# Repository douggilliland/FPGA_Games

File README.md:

# FPGA Games gathered from the Internet

Annotated with the source where I could re-find it again.

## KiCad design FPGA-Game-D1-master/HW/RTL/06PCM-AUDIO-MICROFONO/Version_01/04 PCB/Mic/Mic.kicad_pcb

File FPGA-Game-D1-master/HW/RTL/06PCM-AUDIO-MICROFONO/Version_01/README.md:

# SISTEMA DE AUDIO

## Integrantes del equipo de trabajo:

### 1 Lisseth Tatiana Herrera Rosero ltherreraro@unal.edu.co

### 2 Santiago Esteban Guevara Rozo seguevarar@unal.edu.co

### 3 Michael Fabian Sierra Tarazona mfsierrat@unal.edu.co

## Descripción general del sistema: 

En el módulo de audio se pretende garantizar la grabación de una voz por un lapso aproximado de 2 segundos,  digitalizar, guardar y reproducir esta señal, se utilizaran dos grandes modulos en el cual se tienen microfono y altavoz
En el módulo del micrófono se tendrá una señal análoga con frecuencia de 1 a 5 kHz, la cual entrará a un convertidor A/D, acontinuación se procesará en un filtro pasabajos logrando una salida de 18 bits; Esta entrará a nuestra FPGA nexys4 donde se guardará por módulos en un proceso FIFO sincrónico, el sincronismo de los clocks es necesario para acoplar todas las fases de dicho proceso.
En la segunda etapa (altavoz), entra dicha informacion a un convertidor D/A (PCM) el cual también logra amplificar esta señal para poder ser reproducida.

## Descripción de la caja funcional (Modulo Microfono):
En este módulo depende del modulo divisor de frecuencia. El divisor de frecuencia es necesario para obtener los clocks de sincranización de el módulo de micrófono y de altavoz.

Este modulo tiene entradas: 
* **Data** datos provenientes del micrófono (conformado por 32 bits) de los cuales solo 18 se van a usar para la salida 
* **Enable** para inicializar (conformado por 1 bit)

Este módulo tiene salidas:
* **Clk** El clock que necesita el micrófono para modular la señal y enviarla (conformado por 1 bit)
* **ws** necesario más adelante para seleccionar derecho o izquierdo (conformado por 1 bit)
* **Dataout** datos de salida serializado (conformado por 1 bit)
* **done** para indicar que finalizó la acción (conformado por 1 bit)

Y finalmente tiene un parametro
* **Count** para contar las interacciones 

### Descripción funcional (Módulo Micrófono MEMS):
Para que el modulo de microfono este activo la frecuencia del clk debe estar ser mayor a 1MHz y tener el voltaje VDD activo, pero esto se garantiza en el divisor de frecuencia.

## Descripción de la caja funcional (Modulo Altavoz):
En este módulo tambien depende de el modulo divisor de frecuencia. 

Este modulo tiene entradas: 
* **Data** datos provenientes del micrófono ya serializados (conformado por 1 bit) 
* **Enable** para inicializar (conformado por 1 bit)

Este módulo tiene salidas:
* **Bclk** El clock que necesita el altavoz para recuperar los datos(conformado por 1 bit)
* **LRclk** necesario para seleccionar derecho o izquierdo (conformado por 1 bit)
* **Data_R** datos de salida canal derecho (conformado por 16 bit)
* **Data_L** datos de salida canal izquierdo (conformado por 16 bit)
* **done** para indicar que finalizó la acción (conformado por 1 bit)

Y finalmente tiene un parametro
* **Count** para contar las interacciones 

### Descripción funcional (Módulo Altavoz):
El LRclk tiene un delay de 1 ciclo de Bclk por lo tanto solo soporta frecuencias de 8KHz, 16KHz, 32KHz, 44.1KHz, 48KHz, 88.2KHz y 96KHz, pero esto se garantiza en el divisor de frecuencia.

## Descripción de la caja funcional (Módulo Divisor de frecuencia):
Este modulo tiene entradas: 
* **Clk** El clock que necesita realizar la divison de señal (conformado por 1 bit)
* **Reset** para reiniciar el sistema (conformado por 1 bit)

Este módulo tiene salidas:
* **Clkout** El clock que se deseaba (conformado por 1 bit)
Y finalmente tiene como parametros
* **fi** Frecuencia de entrada
* **fo** Frecuencia de salida (la que se desea obtener)
* **Count** para contar las interacciones 

### Descripción funcional (Divisor de frecuencia):

## Descripción Estructural: 

## Diagrama de Estados:

### Diagrama de estado del MEMS:

### Diagrama de estado del altavoz:

## Arquitectura del periférico:

XXXXXXXXXXXXXXXXXXXXXXXXXXXXXXXXXXXXXXXXXXXXXXXXXX

## Diagrama de bloques del periférico:

XXXXXXXXXXXXXXXXXXXXXXXXXXXXXXXXXXXXXXXXXXXXXXXXXX

## referencias:
-Datasheet Microfono mems SPH0645LM4H-B,[online] knowls, Disponible en: https://www.digikey.com/product-detail/es/knowles/SPH0645LM4H-B/423-1405-1-ND/5332432
-Datasheet Nexys 4TM FPGA Board Reference Manual,[online], Digilent Disponible en: http://store.digilentinc.com/nexys-4-artix-7-fpga-trainer-board-limited-time-see-nexys4-ddr/
-Datasheet PCM Audio MAX98357A,[online] Maxim integrated, Disponible en:http://www.alldatasheet.com/view.jsp?Searchword=Max98357a

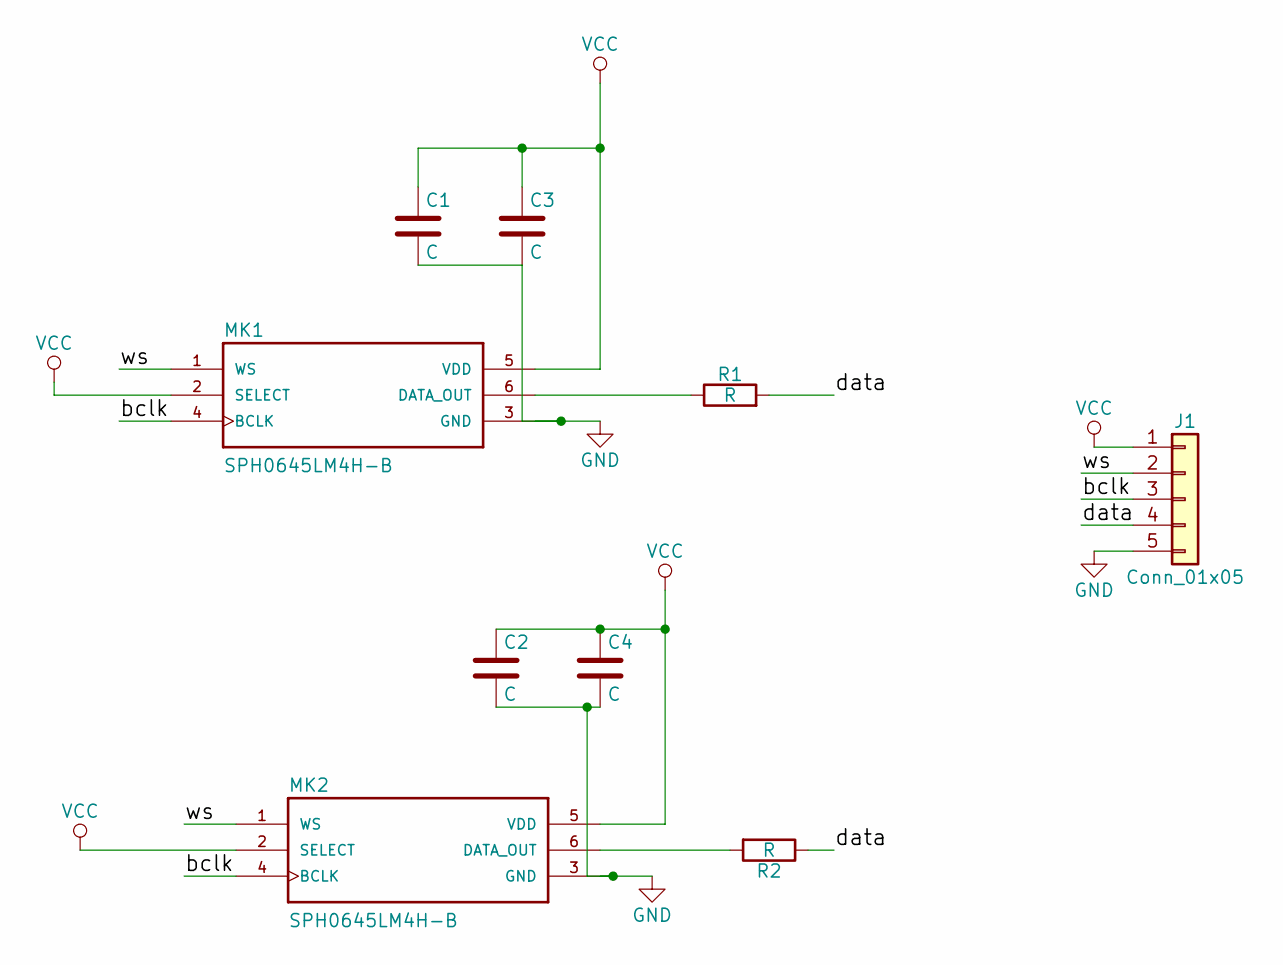
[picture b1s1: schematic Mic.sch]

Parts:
C1, C2, C3, C4: C; C_0805_HandSoldering
J1: Conn_01x05; Pin_Header_Straight_1x05_Pitch1.00mm
MK1, MK2: SPH0645LM4H-B; MIC_SPH0645LM4H-B
R1, R2: R; R_0805_HandSoldering

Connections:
/bclk: J1.3, MK1.4 (BCLK), MK2.4 (BCLK)
/data: J1.4, R1.2, R2.1
/ws: J1.2, MK1.1 (WS), MK2.1 (WS)
GND: C1.2, C2.2, C3.2, C4.2, J1.5, MK1.3 (GND), MK2.3 (GND)
unnamed: MK1.6 (DATA_OUT), R1.1
unnamed: MK2.6 (DATA_OUT), R2.2
VCC: C1.1, C2.1, C3.1, C4.1, J1.1, MK1.2 (SELECT), MK1.5 (VDD), MK2.2 (SELECT), MK2.5 (VDD)

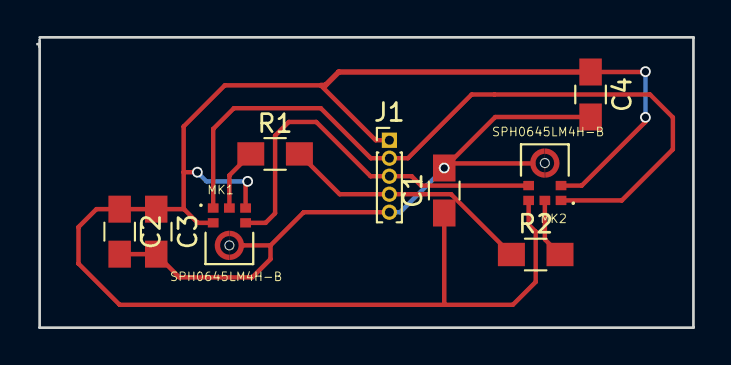
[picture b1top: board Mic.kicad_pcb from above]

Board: 2 copper layers, 36.4 x 16.1 mm, 9 parts (0 on the bottom side), 7 nets.

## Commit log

2019-05-26 Gathering games from the internet
2019-05-26 More games
2019-05-26 More FPGA games from the Internet
2019-05-26 More FPGA games
2019-05-26 Game of Life
2019-05-26 Arkanoid in FPGA
2019-05-26 Sokoban
2019-05-26 car shooter game
2019-05-26 Helicopter game
2019-05-26 maze
2019-05-26 tetris
2019-05-26 games
2019-05-26 Collected a bunch of games
2019-11-22 AY sound
2020-01-31 pacman
2020-08-16 update tetris?
2021-07-16 Tried to build without success
2022-08-19 Defender game
